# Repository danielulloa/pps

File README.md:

# Semana 1
Comienza PPS el 17/03/22. Dentro de los objetivos a corto plazo se tiene la utilización de los variadores disponibles en el laboratorio, el uso del analizador de calidad de energía, el diagnóstico y puesta en marcha de un Plotter ENCAD ENJET 4. Los objetivos a largo plazo son la medición y adquisición de tensiones y corrientes transitorias, la documentación de los resultados obtenidos durante la realización de la pasantía y proponer nuevas actividades de laboratorio.

Las pruebas que se realizaron en el plotter indican que la correa principal del carro está dañada, no existe repuesto de la misma. Los variadores disponibles son dos, uno es de la marca ABB modelo SAMI MS y otro es de la marca Schneider modelo Altivar 312. El analizador de calidad de energía es un Metrel MI 2092. No hay documentación online disponible del variador ABB, solo una fotocopia de un manual.

# Semana 2
Reconocimiento de los insumos y herramientas disponibles en el laboratorio. En cuanto a herramientas e instrumentos específicos para electrónica se encuentra un osciloscopio BK Precision 1590A, un generador de funciones, un soldador con temperatura ajustable, fuente de alimentación ajustable y una fuente de alimentación simétrica. Se identificaron los contactores disponibles, muchos de ellos son antiguos y se desconoce la vida útil restante, mientras que los nuevos, en caja, no pueden ser utilizados por falta de transformadores de 24V. Entre la variedad de elementos de maniobra y señalización se observa la ausencia de indicadores tipo ojo de buey de 22mm.

Se identificaron los motores que podrían ser utilizados con variador de frecuencia electrónico ABB Sami MS y Schneider Altivar 312. Lectura sobre arranque de motores y control de velocidad en el libro "Máquinas Eléctricas - Theodore Wildi". Fabricación de bobina Rogowski y posterior prueba con carga resistiva monofásica.

# Semana 3
Arranque de motor asincrónico con contactor, uso del analizador de calidad de energía Metrel MI 2092, conexión a PC del analizador. Se analizó la posibilidad de medir la corriente de arranque del motor con el instrumento, la tasa de actualización mínima es de 1 segundo y las pinzas de corriente disponibles no son adecuadas para medir corrientes pequeñas.
Se propone la reutilización de un banco de trabajo con tableros adecuados para:
  * Arranque directo con contactor, incluir guardamotor de 0.9A a 1.25A. Además de aprender a cablear un contactor, se puede realizar la medición de la corriente a torque nominal y ajustar el guardamotor para proteger al motor.
  * Freno de corriente continua, introducción al principio de frenado con aplicación de corriente continua a uno de los devanados del motor.
  * Uso de variador, rampas de aceleración, torque de arranque máximo.

Cableado y puesta en marcha del variador SAMI, armado de un nuevo panel de comando externo, no fue posible realizar comunicación con la PC mediante RS485 ya que no se dispone de la información ni software necesario para dicha tarea. Este variador puede ser utilizado para que los alumnos realicen las conexiones necesarias, caractericen la curva RPM vs Frecuencia del motor utilizando un tacómetro y verifiquen la respuesta lineal entre la frecuencia y el voltaje del variador. Se podría configurar la salida analógica 4-20mA (terminales 14 y 15) del variador para indicar la corriente de salida (Grupo de parámetros 02, opción 4) y con un amperímetro registar la corriente, de esta manera se podría realizar una curva corriente vs RPM del motor.

# Semana 4
Comunicación por protocolo MODBUS con el variador Altivar 312, instalación y uso del software SoMove. Este variador puede ser utilizado para que los alumnos se familiaricen con la adquisición de datos y la configuración de variadores modernos utilizando un bus de campo.

Implementación, en computadora personal, de DokuWiki, un servicio web para la gestión de documentación de los resultados obtenidos.

Comienza investigación para la implementación de un módulo de adquisición de tensiones y corrientes trifásicas. Entre las características principales se propone:
  * Uso de microcontrolador de bajo costo (ESP8266, ESP32, Arduino Uno, Raspberry Pico)
  * Aislación galvánica
  * Estampas de tiempo al inicio y fin de la medición
  * Alimentación a batería
  * Almacenamiento en tarjeta SD

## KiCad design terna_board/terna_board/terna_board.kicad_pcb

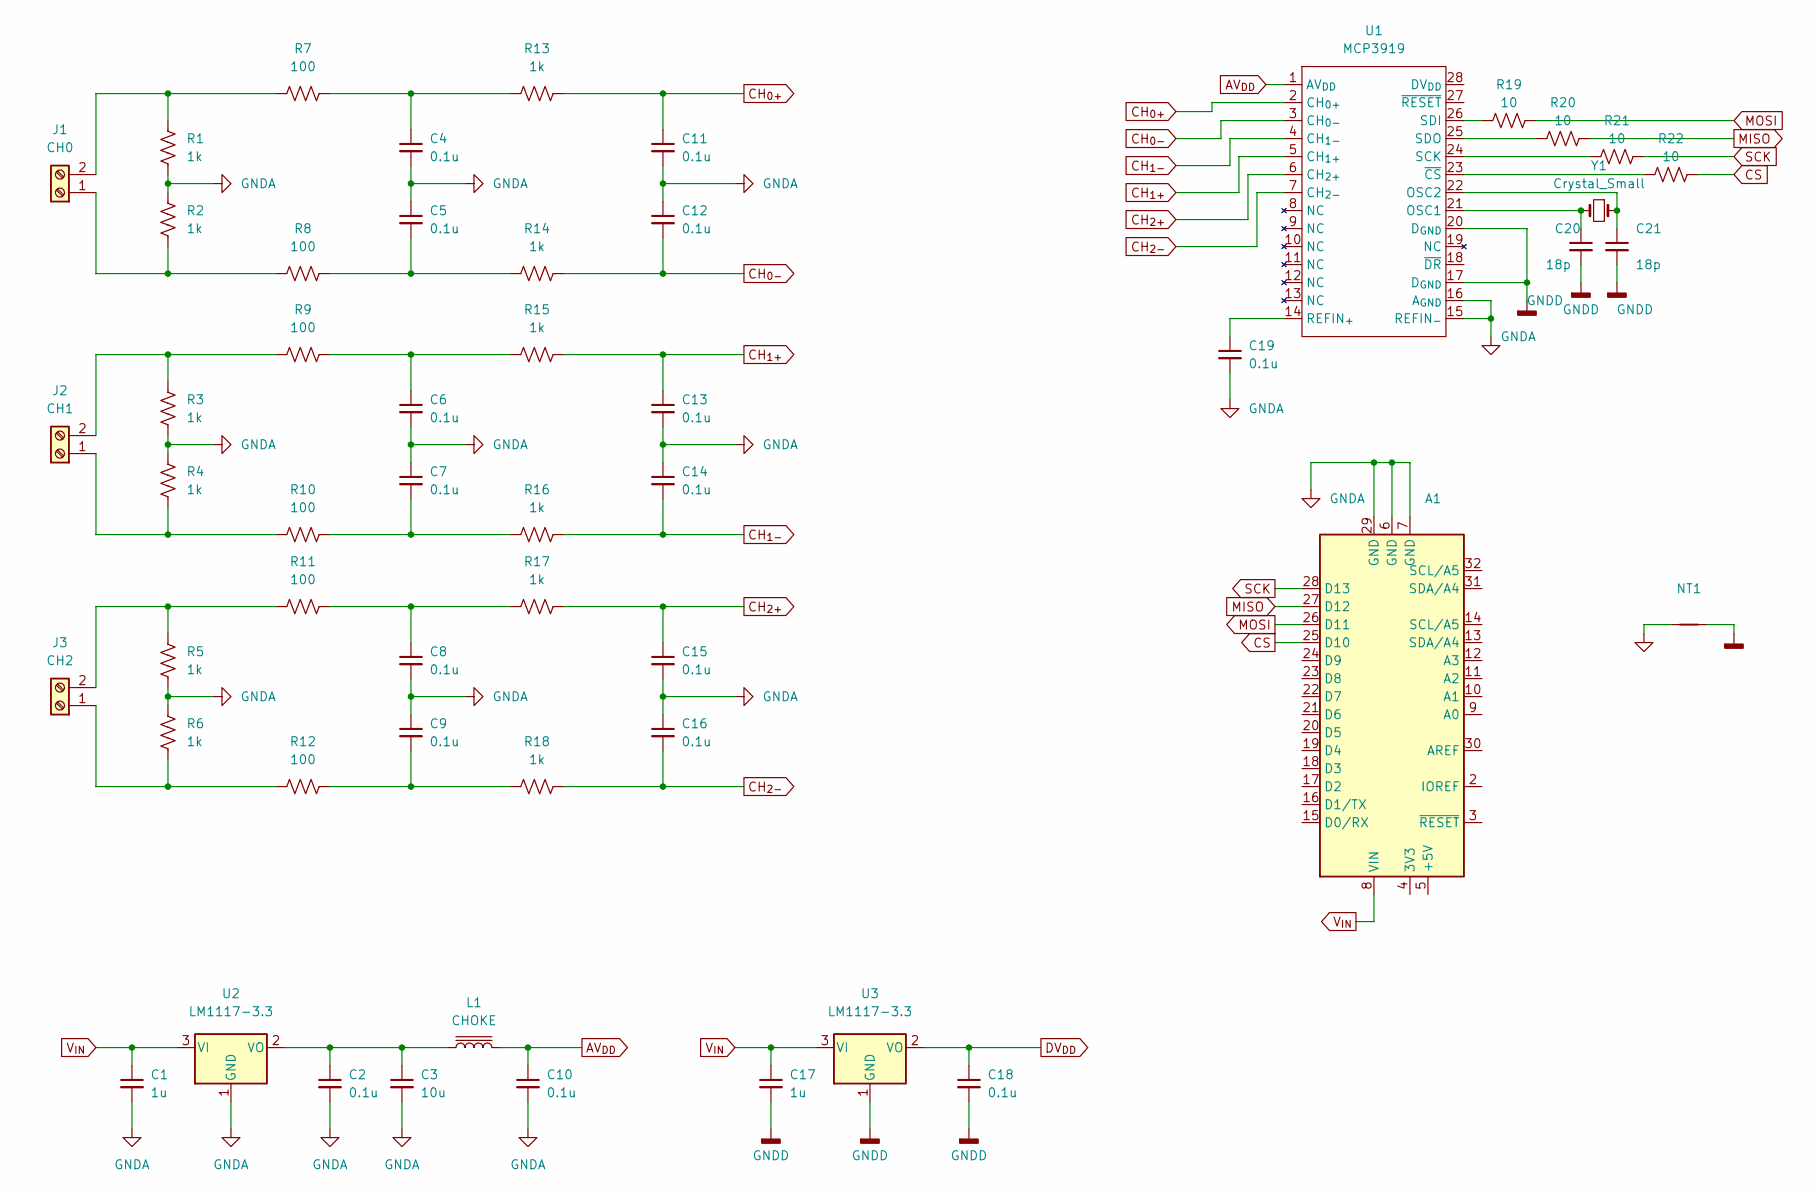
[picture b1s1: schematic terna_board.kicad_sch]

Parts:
A1: (no value)
C1, C17: 1u
C2, C4, C5, C6, C7, C8, C9, C10, C11, C12, C13, C14, C15, C16, C18, C19: 0.1u
C3: 10u
C20, C21: 18p
J1: CH0
J2: CH1
J3: CH2
L1: CHOKE
NT1: (no value)
R1, R2, R3, R4, R5, R6, R13, R14, R15, R16, R17, R18: 1k
R7, R8, R9, R10, R11, R12: 100
R19, R20, R21, R22: 10
U1: MCP3919; SSOP-28_5.3x10.2mm_P0.65mm
U2, U3: LM1117-3.3
Y1: Crystal_Small

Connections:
AV_{DD}: C10.1, L1.2, U1.1 (AV_{DD})
CH_{0+}: C11.1, R13.2, U1.2 (CH_{0+})
CH_{0-}: C12.2, R14.2, U1.3 (CH_{0-})
CH_{1+}: C13.1, R15.2, U1.5 (CH_{1+})
CH_{1-}: C14.2, R16.2, U1.4 (CH_{1-})
CH_{2+}: C15.1, R17.2, U1.6 (CH_{2+})
CH_{2-}: C16.2, R18.2, U1.7 (CH_{2-})
CS: A1.25 (D10), R22.2
DV_{DD}: C18.1, U3.2 (VO)
MISO: A1.27 (D12), R20.2
MOSI: A1.26 (D11), R19.2
unnamed: C2.1, C3.1, L1.1, U2.2 (VO)
unnamed: C4.1, R7.2, R13.1
unnamed: C5.2, R8.2, R14.1
unnamed: C6.1, R9.2, R15.1
unnamed: C7.2, R10.2, R16.1
unnamed: C8.1, R11.2, R17.1
unnamed: C9.2, R12.2, R18.1
unnamed: J1.1, R2.2, R8.1
unnamed: J1.2, R1.1, R7.1
unnamed: J2.1, R4.2, R10.1
unnamed: J2.2, R3.1, R9.1
unnamed: J3.1, R6.2, R12.1
unnamed: J3.2, R5.1, R11.1
unnamed: C19.1, U1.14 (REFIN_{+})
unnamed: C20.1, U1.21 (OSC1), Y1.2
unnamed: C21.1, U1.22 (OSC2), Y1.1
unnamed: R22.1, U1.23 (~CS)
unnamed: R21.1, U1.24 (SCK)
unnamed: R20.1, U1.25 (SDO)
unnamed: R19.1, U1.26 (SDI)
SCK: A1.28 (D13), R21.2
V_{IN}: A1.8 (VIN), C1.1, C17.1, U2.3 (VI), U3.3 (VI)

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
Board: 2 copper layers, 52 parts (0 on the bottom side), 31 nets, no tracks yet.

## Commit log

2022-04-11 comienza biblioteca MCP3919
2022-04-12 ordena documentacion y continua registros MCP3919
2022-04-13 prueba mcp3919 micropython
2022-04-13 spreadsheet registros
2022-05-10 agrega pcb y rogowski
